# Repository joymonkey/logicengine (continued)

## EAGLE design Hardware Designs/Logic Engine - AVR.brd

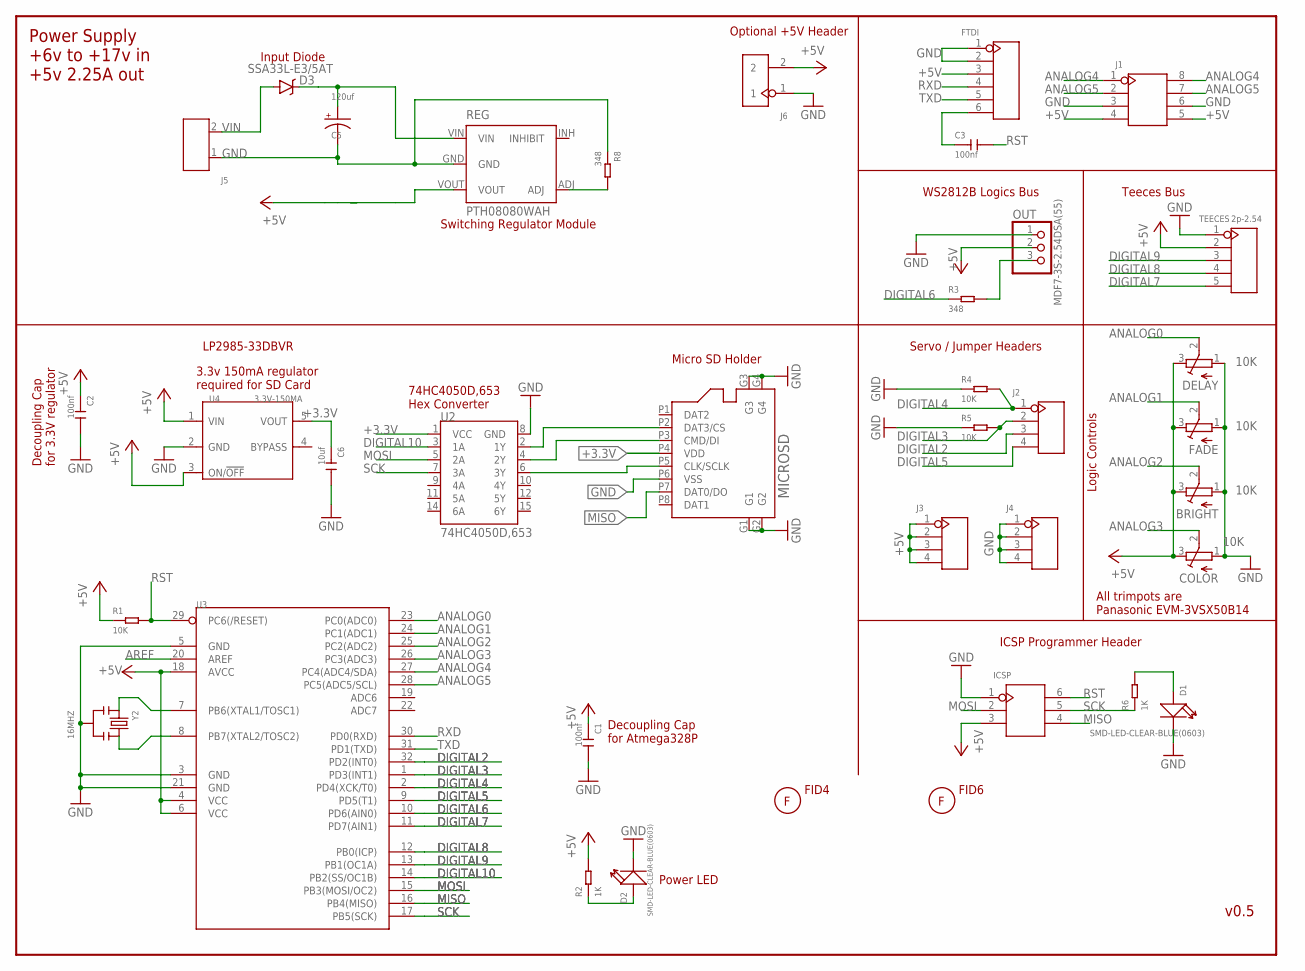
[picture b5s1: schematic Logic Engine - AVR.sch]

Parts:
BRIGHT: 10K; EVM3V
C1, C2, C3: 100nf; C0805
C5: 120uf; PANASONIC_D
C6: 10uf; C0805
COLOR: 10K; EVM3V
D1, D2: SMD-LED-CLEAR-BLUE(0603); LED-0603
D3: SSA33L-E3/5AT; SMA-DIODE
DELAY: 10K; EVM3V
FADE: 10K; EVM3V
FID4, FID6: FIDUCIAL; FIDUCIAL_G15
FTDI: DIP-BLACK-MALE-HEADER(6P-2.54); H6-2.54
ICSP: DIP-BLACK-MALE-HEADER(2X3P-2.54）-2.54; H2X3-2.54
J1: DIP-BLACK-MALE-HEADER-VERT(2X4P-2.54); H2X4-2.54
J2, J3, J4: DIP-BLACK-MALE-HEADER-VERT(4P-2.54); H4-2.54
J5: SCREW-TERMINAL-GREEN(2P-3.5); H2-3.5-7.0X7.0MM
J6: DIP-BLACK-MALE-HEADER-VERT(2P-2.54); H2-2.54
MICROSD: MICROSD47579-001; SD-47579-001
OUT: MDF7-3S-2.54DSA(55); MDF7_1X03
R1, R4, R5: 10K; R0603
R2, R6: 1K; R0603
R3, R8: 348; R0603
REG: PTH08080WAH; PTH08080W_TH
TEECES: 2p-2.54; H5-2.54
U2: 74HC4050D,653; SO016
U3: MCU-ATMEGA328P-AU(TQFP32); TQFP32-0.8-7X7MM
U4: 3.3V-150MA; SOT-23-5; MPN LP2985-33DBVR
Y2: 16MHZ; X3-SMD-3.6X1.3X0.8MM

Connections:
+3.3V: C6.1, MICROSD.P4 (VDD), U2.1 (VCC), U4.5 (VOUT)
+5V: BRIGHT.3 (E), C1.1, C2.1, COLOR.3 (E), DELAY.3 (E), FADE.3 (E), FTDI.3, ICSP.3, J1.4, J1.5, J3.1, J3.2, J3.3, J3.4, J6.2, OUT.2, R1.1, R2.2, REG.VOUT, TEECES.2, U3.4 (VCC), U3.6 (VCC), U3.18 (AVCC), U4.1 (VIN), U4.3 (ON/!OFF)
ANALOG0: DELAY.2 (S), U3.23 (PC0(ADC0))
ANALOG1: FADE.2 (S), U3.24 (PC1(ADC1))
ANALOG2: BRIGHT.2 (S), U3.25 (PC2(ADC2))
ANALOG3: COLOR.2 (S), U3.26 (PC3(ADC3))
ANALOG4: J1.1, J1.8, U3.27 (PC4(ADC4/SDA))
ANALOG5: J1.2, J1.7, U3.28 (PC5(ADC5/SCL))
AREF: U3.20 (AREF)
CS: MICROSD.P2 (DAT3/CS), U2.2 (1Y)
DATA_IN: MICROSD.P3 (CMD/DI), U2.4 (2Y)
DIGITAL2: J2.3, U3.32 (PD2(INT0))
DIGITAL3: J2.2, R5.2, U3.1 (PD3(INT1))
DIGITAL4: J2.1, R4.2, U3.2 (PD4(XCK/T0))
DIGITAL5: J2.4, U3.9 (PD5(T1))
DIGITAL6: R3.1, U3.10 (PD6(AIN0))
DIGITAL7: TEECES.5, U3.11 (PD7(AIN1))
DIGITAL8: TEECES.4, U3.12 (PB0(ICP))
DIGITAL9: TEECES.3, U3.13 (PB1(OC1A))
DIGITAL10: U2.3 (1A), U3.14 (PB2(SS/OC1B))
GND: BRIGHT.1 (A), C1.2, C2.2, C5.-, C6.2, COLOR.1 (A), D1.-, D2.-, DELAY.1 (A), FADE.1 (A), FTDI.1, FTDI.2, ICSP.1, J1.3, J1.6, J4.1, J4.2, J4.3, J4.4, J5.1, J6.1, MICROSD.G1, MICROSD.G2, MICROSD.G3, MICROSD.G4, MICROSD.P6 (VSS), OUT.1, R4.1, R5.1, R8.1, REG.GND, TEECES.1, U2.8 (GND), U3.3 (GND), U3.5 (GND), U3.21 (GND), U4.2 (GND), Y2.2
MISO: ICSP.4, MICROSD.P7 (DAT0/DO), U3.16 (PB4(MISO))
MOSI: ICSP.2, U2.5 (2A), U3.15 (PB3(MOSI/OC2))
unnamed: C5.+, D3.C, REG.VIN
unnamed: D1.+, R6.2
unnamed: D2.+, R2.1
unnamed: R8.2, REG.ADJ
unnamed: OUT.3, R3.2
unnamed: U3.7 (PB6(XTAL1/TOSC1)), Y2.1
unnamed: U3.8 (PB7(XTAL2/TOSC2)), Y2.3
RST: C3.2, ICSP.6, R1.2, U3.29 (PC6(/RESET))
RTS#: C3.1, FTDI.6
RXD: FTDI.4, U3.30 (PD0(RXD))
SCK: ICSP.5, R6.1, U2.7 (3A), U3.17 (PB5(SCK))
SCLK: MICROSD.P5 (CLK/SCLK), U2.6 (3Y)
TXD: FTDI.5, U3.31 (PD1(TXD))
VIN: D3.A, J5.2

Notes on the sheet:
v0.5
WS2812B Logics Bus
Power Supply +6v to +17v in +5v 2.25A out
Logic Controls
Teeces Bus
3.3v 150mA regulator required for SD Card
Servo / Jumper Headers
Optional +5V Header
74HC4050D,653 Hex Converter
LP2985-33DBVR
All trimpots are Panasonic EVM‑3VSX50B14
Micro SD Holder
Switching Regulator Module
Input Diode
Decoupling Cap for Atmega328P
Decoupling Cap for 3.3V regulator
ICSP Programmer Header
Power LED

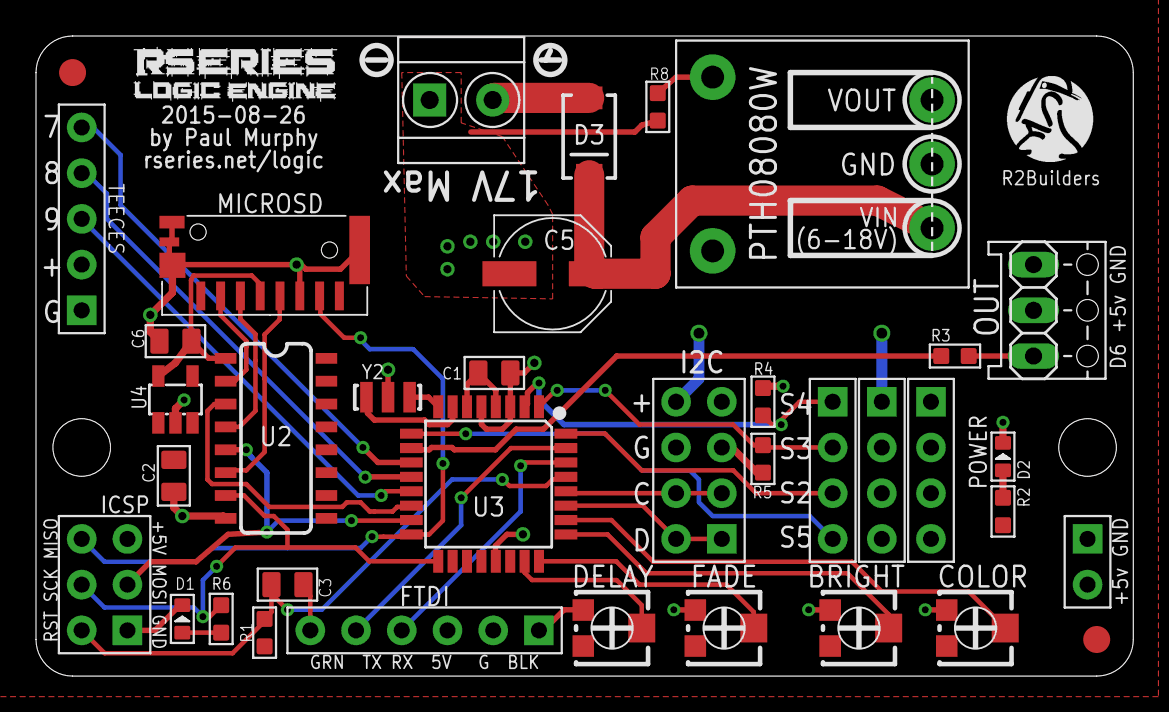
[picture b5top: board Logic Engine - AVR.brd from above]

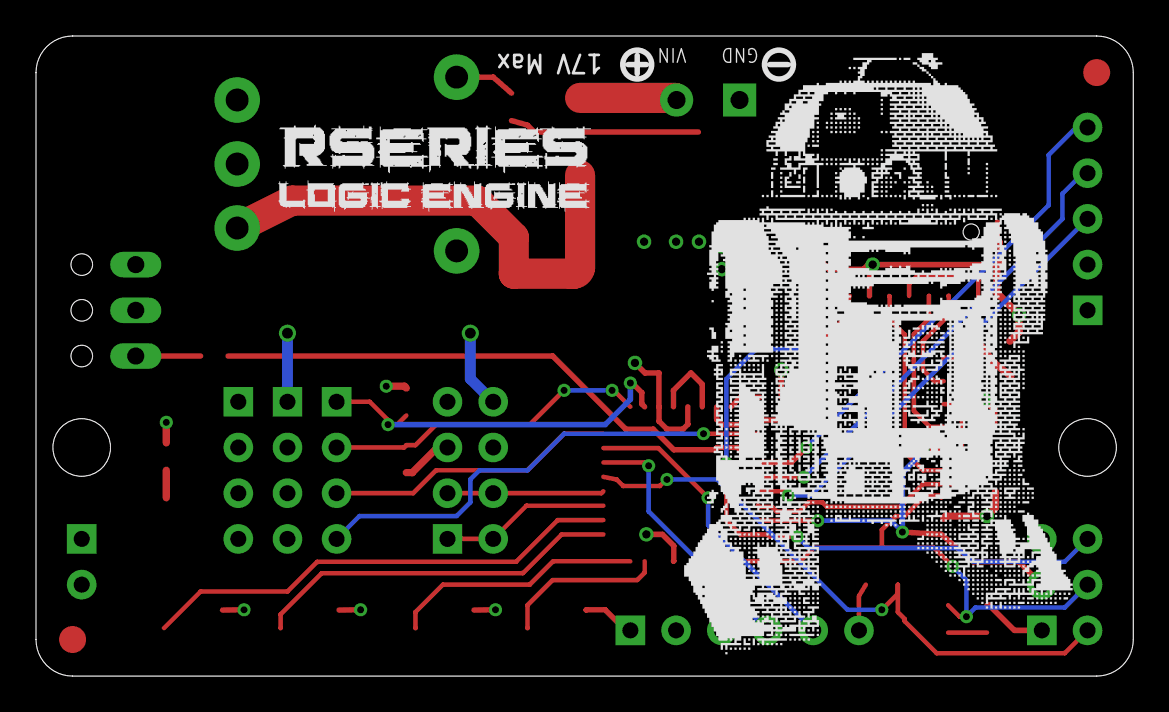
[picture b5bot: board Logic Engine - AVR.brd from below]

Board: 2 copper layers, 61.0 x 35.6 mm, 41 parts (2 on the bottom side), 36 nets.

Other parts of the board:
U$1: R2BUILDERS-LOGO
U$2: RSERIES-LE-LOGO2
U$3: RSERIES-LE-LOGO
U$4: R2-2LEG

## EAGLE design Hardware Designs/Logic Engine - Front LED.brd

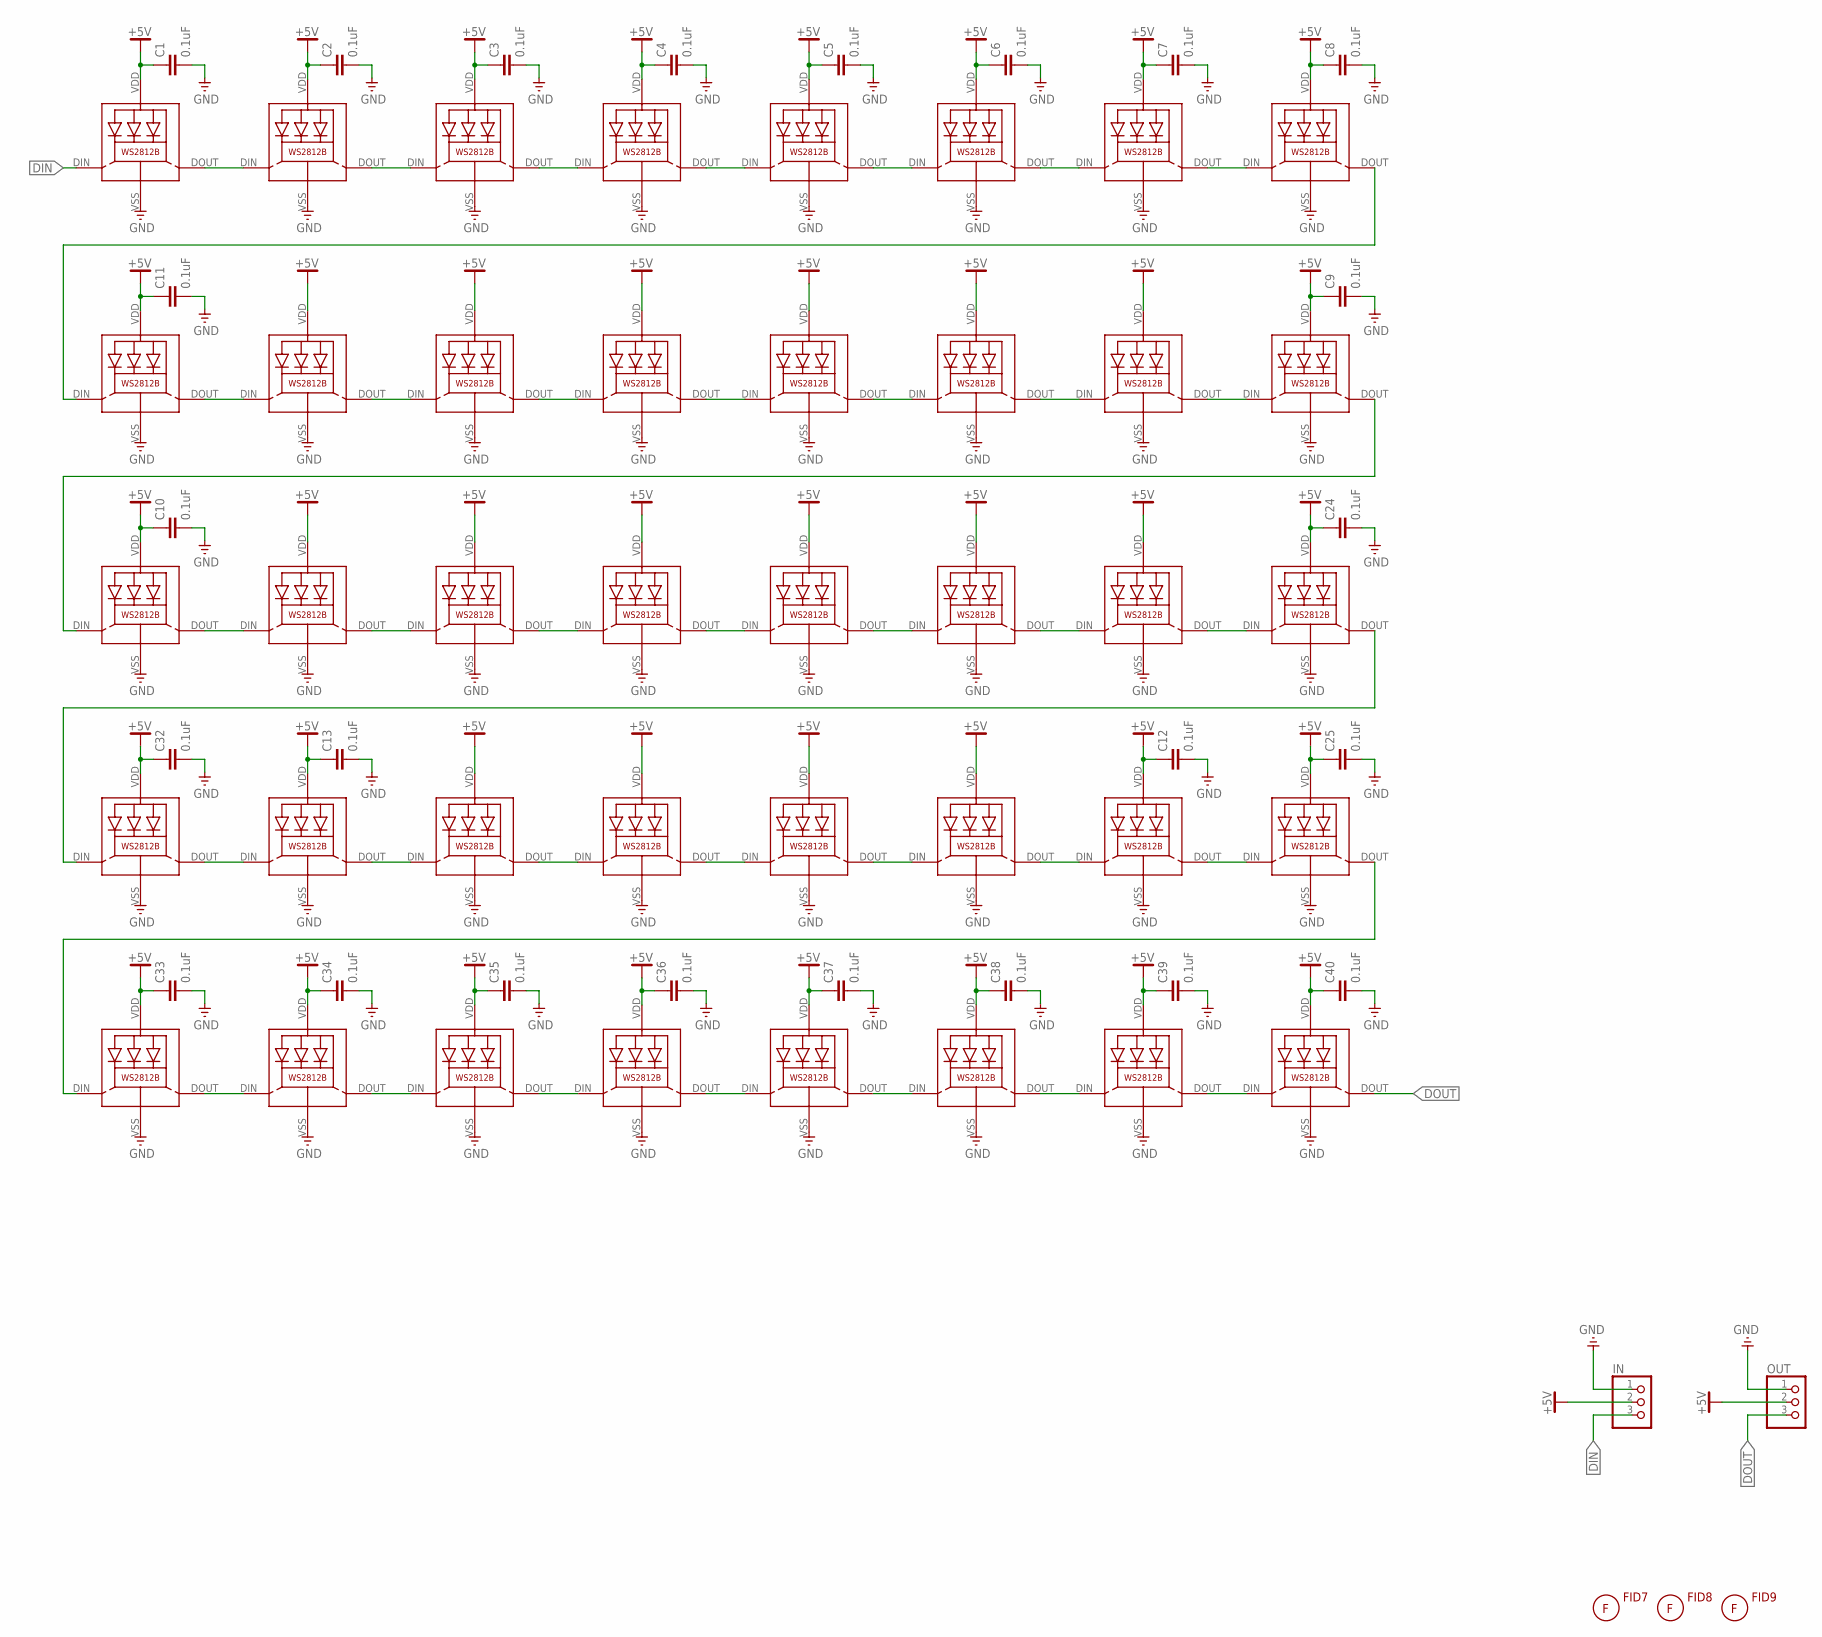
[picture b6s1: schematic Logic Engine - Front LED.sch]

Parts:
C1, C2, C3, C4, C5, C6, C7, C8, C9, C10, C11, C12, C13, C24, C25, C32, C33, C34, C35, C36, C37, C38, C39, C40: 0.1uF; 0603-CAP
FID7, FID8, FID9: FIDUCIAL; FIDUCIAL_G15
IN: PINHD-1X3; 1X03
L1, L2, L3, L4, L5, L6, L7, L8, L9, L10, L11, L12, L13, L14, L15, L16, L17, L18, L19, L20, L21, L22, L23, L24, L25, L26, L27, L28, L29, L30, L31, L32, L33, L34, L35, L36, L37, L38, L39, L40: WS2812B
OUT: PINHD-1X3; 1X03

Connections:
+5V: C1.1, C2.1, C3.1, C4.1, C5.1, C6.1, C7.1, C8.1, C9.1, C10.1, C11.1, C12.1, C13.1, C24.1, C25.1, C32.1, C33.1, C34.1, C35.1, C36.1, C37.1, C38.1, C39.1, C40.1, IN.2, L1.VDD, L2.VDD, L3.VDD, L4.VDD, L5.VDD, L6.VDD, L7.VDD, L8.VDD, L9.VDD, L10.VDD, L11.VDD, L12.VDD, L13.VDD, L14.VDD, L15.VDD, L16.VDD, L17.VDD, L18.VDD, L19.VDD, L20.VDD, L21.VDD, L22.VDD, L23.VDD, L24.VDD, L25.VDD, L26.VDD, L27.VDD, L28.VDD, L29.VDD, L30.VDD, L31.VDD, L32.VDD, L33.VDD, L34.VDD, L35.VDD, L36.VDD, L37.VDD, L38.VDD, L39.VDD, L40.VDD, OUT.2
DIN: IN.3, L1.DIN (DI)
DOUT: L40.DOUT (DO), OUT.3
GND: C1.2, C2.2, C3.2, C4.2, C5.2, C6.2, C7.2, C8.2, C9.2, C10.2, C11.2, C12.2, C13.2, C24.2, C25.2, C32.2, C33.2, C34.2, C35.2, C36.2, C37.2, C38.2, C39.2, C40.2, IN.1, L1.VSS (GND), L2.VSS (GND), L3.VSS (GND), L4.VSS (GND), L5.VSS (GND), L6.VSS (GND), L7.VSS (GND), L8.VSS (GND), L9.VSS (GND), L10.VSS (GND), L11.VSS (GND), L12.VSS (GND), L13.VSS (GND), L14.VSS (GND), L15.VSS (GND), L16.VSS (GND), L17.VSS (GND), L18.VSS (GND), L19.VSS (GND), L20.VSS (GND), L21.VSS (GND), L22.VSS (GND), L23.VSS (GND), L24.VSS (GND), L25.VSS (GND), L26.VSS (GND), L27.VSS (GND), L28.VSS (GND), L29.VSS (GND), L30.VSS (GND), L31.VSS (GND), L32.VSS (GND), L33.VSS (GND), L34.VSS (GND), L35.VSS (GND), L36.VSS (GND), L37.VSS (GND), L38.VSS (GND), L39.VSS (GND), L40.VSS (GND), OUT.1
unnamed: L9.DOUT (DO), L10.DIN (DI)
unnamed: L10.DOUT (DO), L11.DIN (DI)
unnamed: L11.DOUT (DO), L12.DIN (DI)
unnamed: L12.DOUT (DO), L13.DIN (DI)
unnamed: L13.DOUT (DO), L14.DIN (DI)
unnamed: L14.DOUT (DO), L15.DIN (DI)
unnamed: L15.DOUT (DO), L16.DIN (DI)
unnamed: L17.DOUT (DO), L18.DIN (DI)
unnamed: L18.DOUT (DO), L19.DIN (DI)
unnamed: L19.DOUT (DO), L20.DIN (DI)
unnamed: L20.DOUT (DO), L21.DIN (DI)
unnamed: L21.DOUT (DO), L22.DIN (DI)
unnamed: L22.DOUT (DO), L23.DIN (DI)
unnamed: L23.DOUT (DO), L24.DIN (DI)
unnamed: L25.DOUT (DO), L26.DIN (DI)
unnamed: L26.DOUT (DO), L27.DIN (DI)
unnamed: L27.DOUT (DO), L28.DIN (DI)
unnamed: L28.DOUT (DO), L29.DIN (DI)
unnamed: L29.DOUT (DO), L30.DIN (DI)
unnamed: L30.DOUT (DO), L31.DIN (DI)
unnamed: L31.DOUT (DO), L32.DIN (DI)
unnamed: L33.DOUT (DO), L34.DIN (DI)
unnamed: L34.DOUT (DO), L35.DIN (DI)
unnamed: L35.DOUT (DO), L36.DIN (DI)
unnamed: L36.DOUT (DO), L37.DIN (DI)
unnamed: L37.DOUT (DO), L38.DIN (DI)
unnamed: L38.DOUT (DO), L39.DIN (DI)
unnamed: L39.DOUT (DO), L40.DIN (DI)
unnamed: L8.DOUT (DO), L9.DIN (DI)
unnamed: L16.DOUT (DO), L17.DIN (DI)
unnamed: L24.DOUT (DO), L25.DIN (DI)
unnamed: L32.DOUT (DO), L33.DIN (DI)
unnamed: L1.DOUT (DO), L2.DIN (DI)
unnamed: L2.DOUT (DO), L3.DIN (DI)
unnamed: L3.DOUT (DO), L4.DIN (DI)
unnamed: L4.DOUT (DO), L5.DIN (DI)
unnamed: L5.DOUT (DO), L6.DIN (DI)
unnamed: L6.DOUT (DO), L7.DIN (DI)
unnamed: L7.DOUT (DO), L8.DIN (DI)

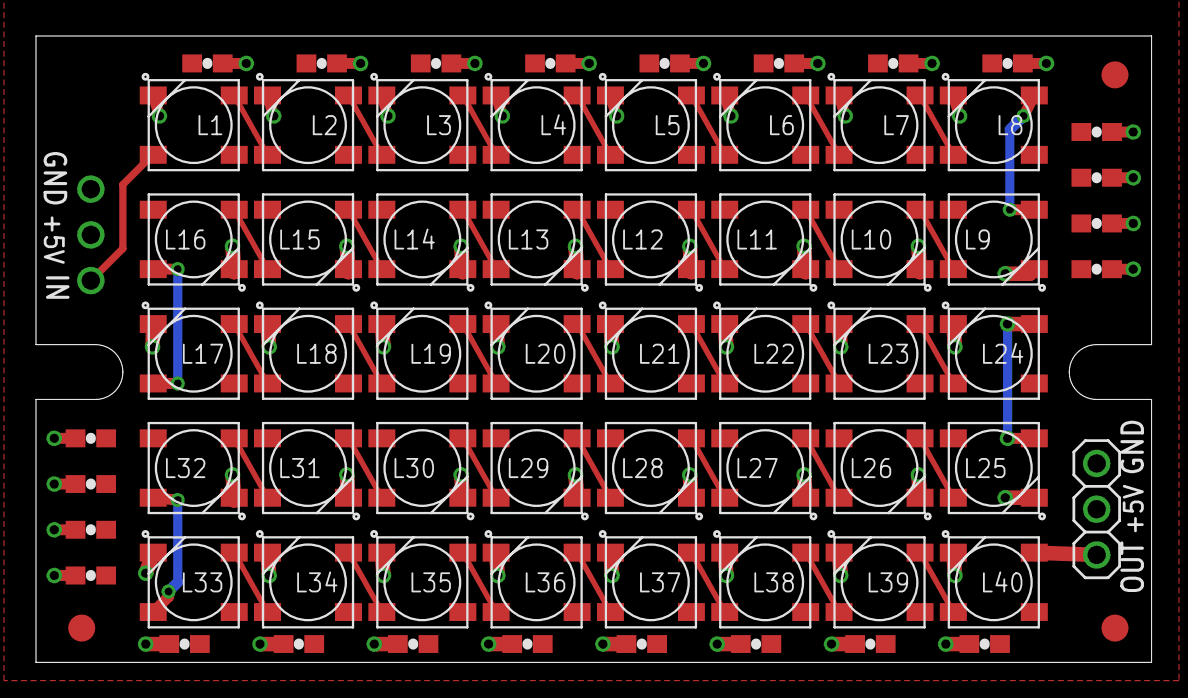
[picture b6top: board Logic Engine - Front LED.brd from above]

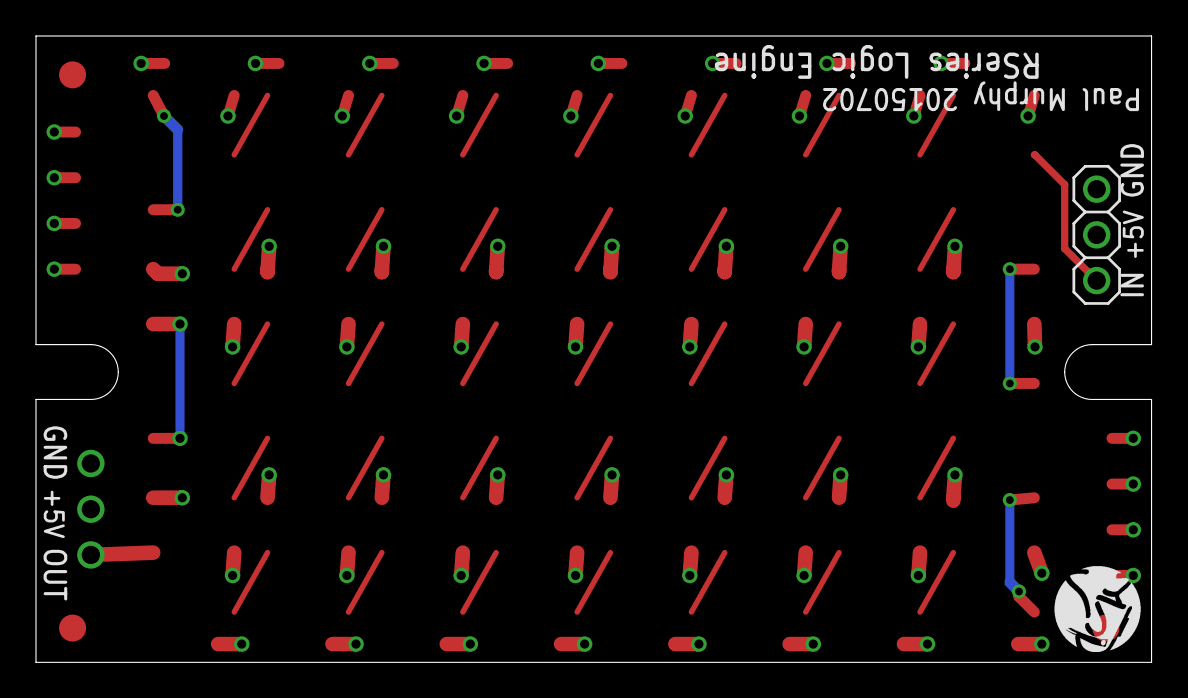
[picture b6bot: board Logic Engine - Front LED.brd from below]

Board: 2 copper layers, 62.0 x 34.8 mm, 70 parts (2 on the bottom side), 43 nets.

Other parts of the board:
U$2: R2BUILDERS-LOGO

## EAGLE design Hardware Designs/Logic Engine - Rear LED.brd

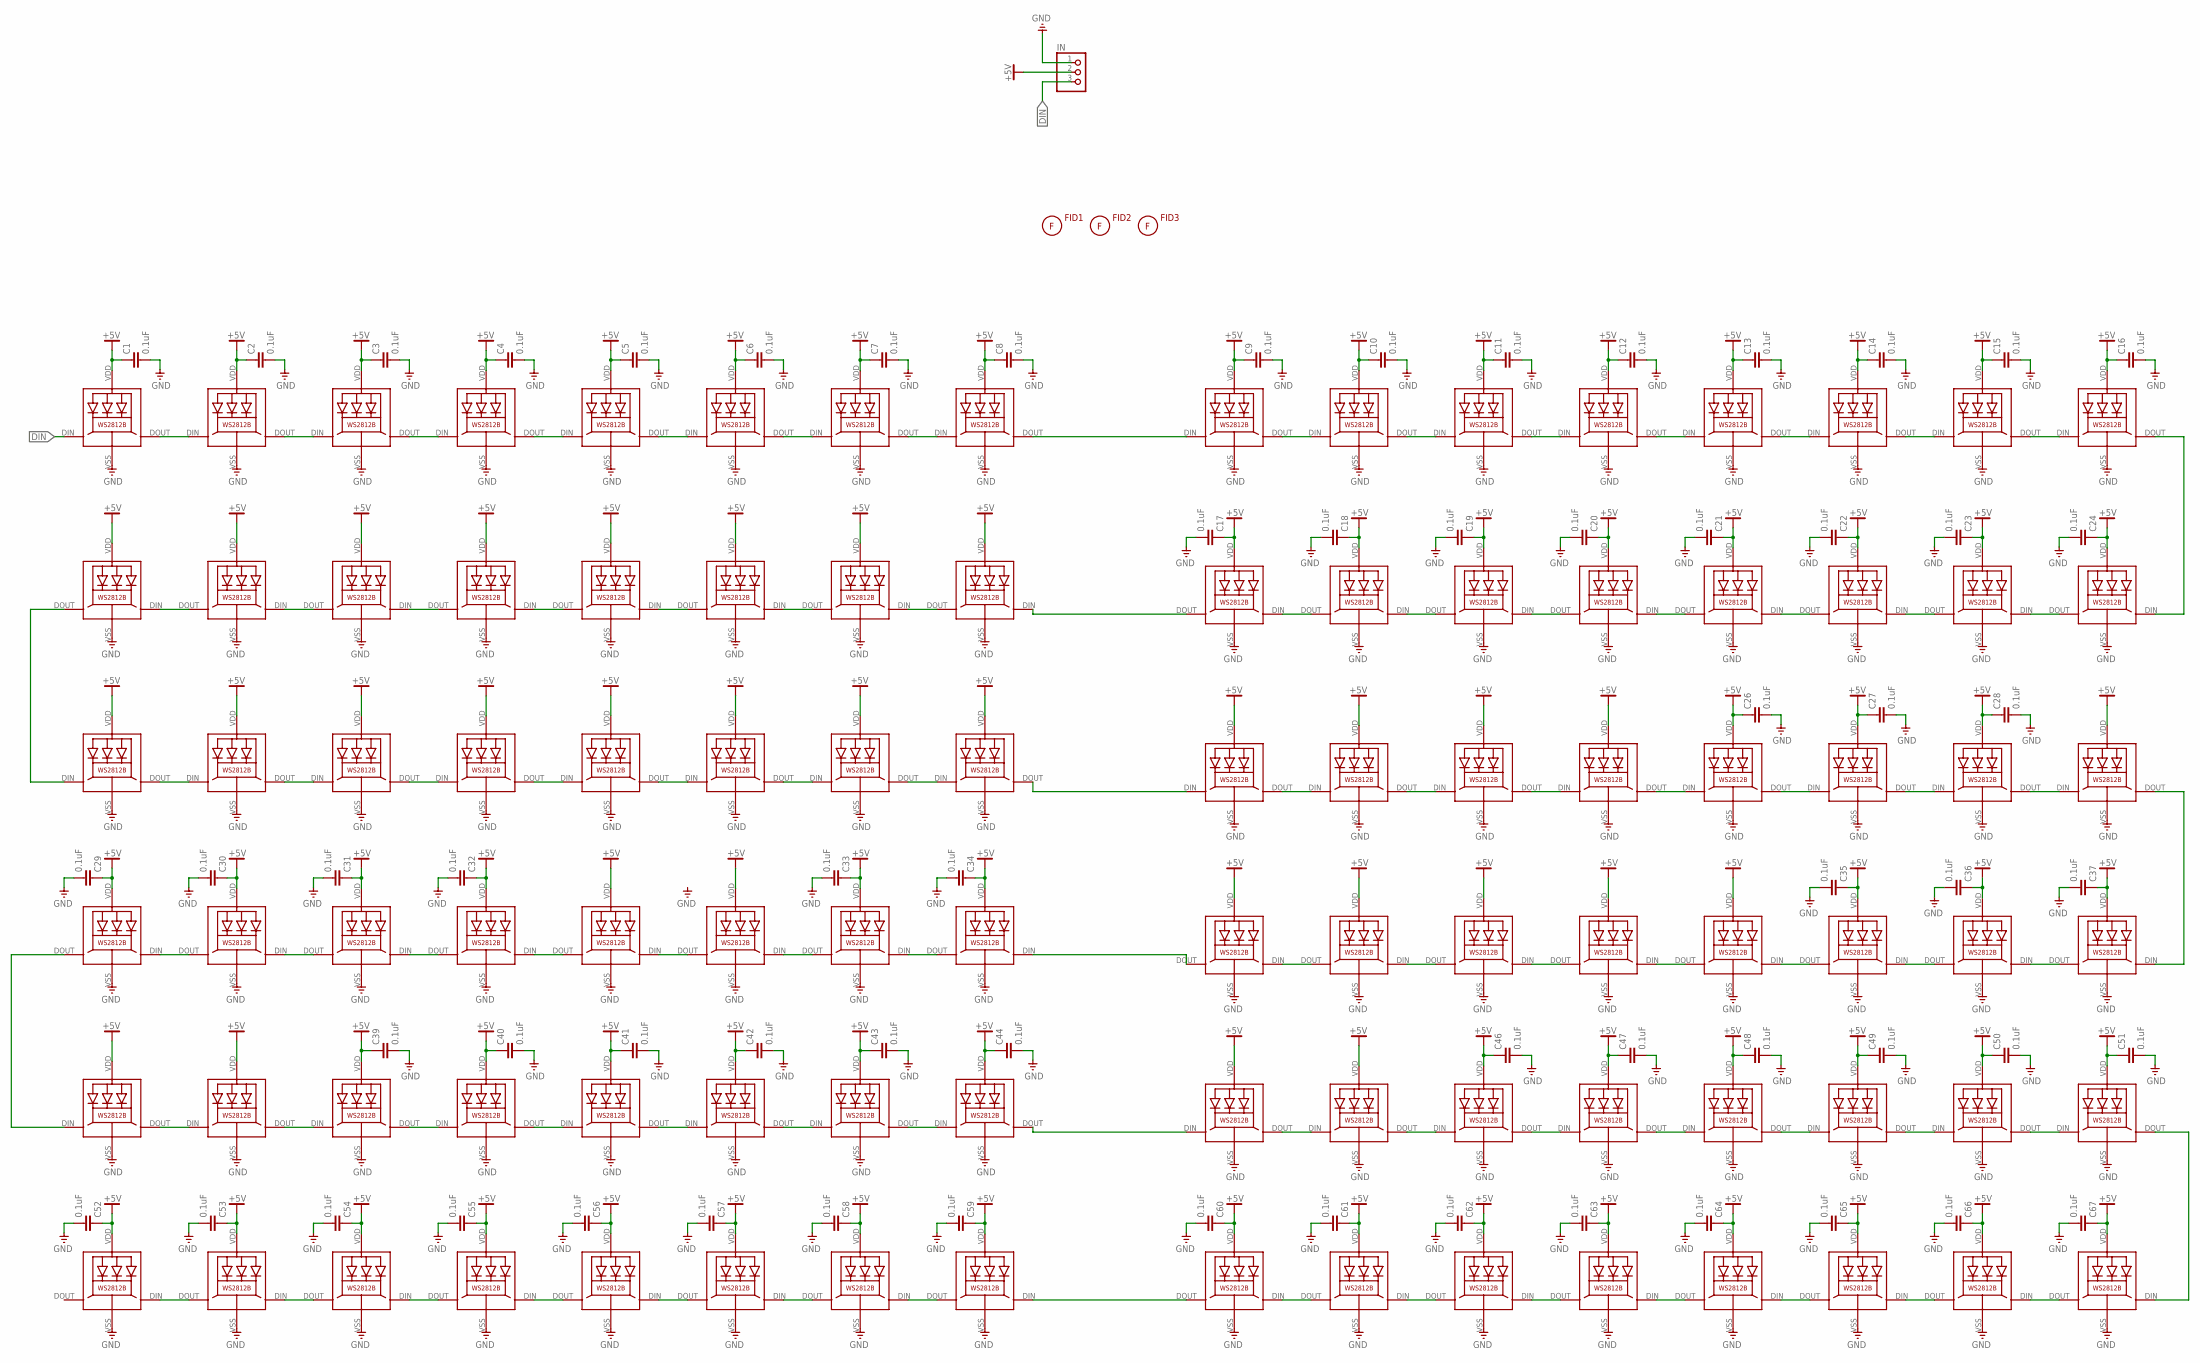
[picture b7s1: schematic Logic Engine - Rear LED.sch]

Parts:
C1, C2, C3, C4, C5, C6, C7, C8, C9, C10, C11, C12, C13, C14, C15, C16, C17, C18, C19, C20, C21, C22, C23, C24, C26, C27, C28, C29, C30, C31, C32, C33, C34, C35, C36, C37, C39, C40, C41, C42, C43, C44, C46, C47, C48, C49, C50, C51, C52, C53, C54, C55, C56, C57, C58, C59, C60, C61, C62, C63, C64, C65, C66, C67: 0.1uF; 0603-CAP
FID1, FID2, FID3: FIDUCIAL; FIDUCIAL_G15
IN: PINHD-1X3; 1X03
L1, L2, L3, L4, L5, L6, L7, L8, L9, L10, L11, L12, L13, L14, L15, L16, L17, L18, L19, L20, L21, L22, L23, L24, L25, L26, L27, L28, L29, L30, L31, L32, L33, L34, L35, L36, L37, L38, L39, L40, L41, L42, L43, L44, L45, L46, L47, L48, L49, L50, L51, L52, L53, L54, L55, L56, L57, L58, L59, L60, L61, L62, L63, L64, L65, L66, L67, L68, L69, L70, L71, L72, L73, L74, L75, L76, L77, L78, L79, L80, L81, L82, L83, L84, L85, L86, L87, L88, L89, L90, L91, L92, L93, L94, L95, L96: WS2812B

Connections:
+5V: C1.1, C2.1, C3.1, C4.1, C5.1, C6.1, C7.1, C8.1, C9.1, C10.1, C11.1, C12.1, C13.1, C14.1, C15.1, C16.1, C17.1, C18.1, C19.1, C20.1, C21.1, C22.1, C23.1, C24.1, C26.1, C27.1, C28.1, C29.1, C30.1, C31.1, C32.1, C33.1, C34.1, C35.1, C36.1, C37.1, C39.1, C40.1, C41.1, C42.1, C43.1, C44.1, C46.1, C47.1, C48.1, C49.1, C50.1, C51.1, C52.1, C53.1, C54.1, C55.1, C56.1, C57.1, C58.1, C59.1, C60.1, C61.1, C62.1, C63.1, C64.1, C65.1, C66.1, C67.1, IN.2, L1.VDD, L2.VDD, L3.VDD, L4.VDD, L5.VDD, L6.VDD, L7.VDD, L8.VDD, L9.VDD, L10.VDD, L11.VDD, L12.VDD, L13.VDD, L14.VDD, L15.VDD, L16.VDD, L17.VDD, L18.VDD, L19.VDD, L20.VDD, L21.VDD, L22.VDD, L23.VDD, L24.VDD, L25.VDD, L26.VDD, L27.VDD, L28.VDD, L29.VDD, L30.VDD, L31.VDD, L32.VDD, L33.VDD, L34.VDD, L35.VDD, L36.VDD, L37.VDD, L38.VDD, L39.VDD, L40.VDD, L41.VDD, L42.VDD, L43.VDD, L44.VDD, L45.VDD, L46.VDD, L47.VDD, L48.VDD, L49.VDD, L50.VDD, L51.VDD, L52.VDD, L53.VDD, L54.VDD, L55.VDD, L56.VDD, L57.VDD, L58.VDD, L59.VDD, L60.VDD, L61.VDD, L62.VDD, L63.VDD, L64.VDD, L65.VDD, L66.VDD, L67.VDD, L68.VDD, L69.VDD, L70.VDD, L71.VDD, L72.VDD, L73.VDD, L74.VDD, L75.VDD, L76.VDD, L77.VDD, L78.VDD, L79.VDD, L80.VDD, L81.VDD, L82.VDD, L83.VDD, L84.VDD, L85.VDD, L86.VDD, L87.VDD, L88.VDD, L89.VDD, L90.VDD, L91.VDD, L92.VDD, L93.VDD, L94.VDD, L95.VDD, L96.VDD
DIN: IN.3, L1.DIN (DI)
GND: C1.2, C2.2, C3.2, C4.2, C5.2, C6.2, C7.2, C8.2, C9.2, C10.2, C11.2, C12.2, C13.2, C14.2, C15.2, C16.2, C17.2, C18.2, C19.2, C20.2, C21.2, C22.2, C23.2, C24.2, C26.2, C27.2, C28.2, C29.2, C30.2, C31.2, C32.2, C33.2, C34.2, C35.2, C36.2, C37.2, C39.2, C40.2, C41.2, C42.2, C43.2, C44.2, C46.2, C47.2, C48.2, C49.2, C50.2, C51.2, C52.2, C53.2, C54.2, C55.2, C56.2, C57.2, C58.2, C59.2, C60.2, C61.2, C62.2, C63.2, C64.2, C65.2, C66.2, C67.2, IN.1, L1.VSS (GND), L2.VSS (GND), L3.VSS (GND), L4.VSS (GND), L5.VSS (GND), L6.VSS (GND), L7.VSS (GND), L8.VSS (GND), L9.VSS (GND), L10.VSS (GND), L11.VSS (GND), L12.VSS (GND), L13.VSS (GND), L14.VSS (GND), L15.VSS (GND), L16.VSS (GND), L17.VSS (GND), L18.VSS (GND), L19.VSS (GND), L20.VSS (GND), L21.VSS (GND), L22.VSS (GND), L23.VSS (GND), L24.VSS (GND), L25.VSS (GND), L26.VSS (GND), L27.VSS (GND), L28.VSS (GND), L29.VSS (GND), L30.VSS (GND), L31.VSS (GND), L32.VSS (GND), L33.VSS (GND), L34.VSS (GND), L35.VSS (GND), L36.VSS (GND), L37.VSS (GND), L38.VSS (GND), L39.VSS (GND), L40.VSS (GND), L41.VSS (GND), L42.VSS (GND), L43.VSS (GND), L44.VSS (GND), L45.VSS (GND), L46.VSS (GND), L47.VSS (GND), L48.VSS (GND), L49.VSS (GND), L50.VSS (GND), L51.VSS (GND), L52.VSS (GND), L53.VSS (GND), L54.VSS (GND), L55.VSS (GND), L56.VSS (GND), L57.VSS (GND), L58.VSS (GND), L59.VSS (GND), L60.VSS (GND), L61.VSS (GND), L62.VSS (GND), L63.VSS (GND), L64.VSS (GND), L65.VSS (GND), L66.VSS (GND), L67.VSS (GND), L68.VSS (GND), L69.VSS (GND), L70.VSS (GND), L71.VSS (GND), L72.VSS (GND), L73.VSS (GND), L74.VSS (GND), L75.VSS (GND), L76.VSS (GND), L77.VSS (GND), L78.VSS (GND), L79.VSS (GND), L80.VSS (GND), L81.VSS (GND), L82.VSS (GND), L83.VSS (GND), L84.VSS (GND), L85.VSS (GND), L86.VSS (GND), L87.VSS (GND), L88.VSS (GND), L89.VSS (GND), L90.VSS (GND), L91.VSS (GND), L92.VSS (GND), L93.VSS (GND), L94.VSS (GND), L95.VSS (GND), L96.VSS (GND)
unnamed: L23.DIN (DI), L24.DOUT (DO)
unnamed: L22.DIN (DI), L23.DOUT (DO)
unnamed: L21.DIN (DI), L22.DOUT (DO)
unnamed: L20.DIN (DI), L21.DOUT (DO)
unnamed: L19.DIN (DI), L20.DOUT (DO)
unnamed: L18.DIN (DI), L19.DOUT (DO)
unnamed: L17.DIN (DI), L18.DOUT (DO)
unnamed: L33.DOUT (DO), L34.DIN (DI)
unnamed: L34.DOUT (DO), L35.DIN (DI)
unnamed: L35.DOUT (DO), L36.DIN (DI)
unnamed: L36.DOUT (DO), L37.DIN (DI)
unnamed: L37.DOUT (DO), L38.DIN (DI)
unnamed: L38.DOUT (DO), L39.DIN (DI)
unnamed: L39.DOUT (DO), L40.DIN (DI)
unnamed: L55.DIN (DI), L56.DOUT (DO)
unnamed: L54.DIN (DI), L55.DOUT (DO)
unnamed: L53.DIN (DI), L54.DOUT (DO)
unnamed: L52.DIN (DI), L53.DOUT (DO)
unnamed: L51.DIN (DI), L52.DOUT (DO)
unnamed: L50.DIN (DI), L51.DOUT (DO)
unnamed: L49.DIN (DI), L50.DOUT (DO)
unnamed: L65.DOUT (DO), L66.DIN (DI)
unnamed: L66.DOUT (DO), L67.DIN (DI)
unnamed: L67.DOUT (DO), L68.DIN (DI)
unnamed: L68.DOUT (DO), L69.DIN (DI)
unnamed: L69.DOUT (DO), L70.DIN (DI)
unnamed: L70.DOUT (DO), L71.DIN (DI)
unnamed: L71.DOUT (DO), L72.DIN (DI)
unnamed: L24.DIN (DI), L25.DOUT (DO)
unnamed: L17.DOUT (DO), L33.DIN (DI)
unnamed: L40.DOUT (DO), L41.DIN (DI)
unnamed: L48.DOUT (DO), L64.DIN (DI)
unnamed: L87.DIN (DI), L88.DOUT (DO)
unnamed: L86.DIN (DI), L87.DOUT (DO)
unnamed: L85.DIN (DI), L86.DOUT (DO)
unnamed: L84.DIN (DI), L85.DOUT (DO)
unnamed: L83.DIN (DI), L84.DOUT (DO)
unnamed: L82.DIN (DI), L83.DOUT (DO)
unnamed: L81.DIN (DI), L82.DOUT (DO)
unnamed: L1.DOUT (DO), L2.DIN (DI)
unnamed: L2.DOUT (DO), L3.DIN (DI)
unnamed: L3.DOUT (DO), L4.DIN (DI)
unnamed: L4.DOUT (DO), L5.DIN (DI)
unnamed: L5.DOUT (DO), L6.DIN (DI)
unnamed: L6.DOUT (DO), L7.DIN (DI)
unnamed: L7.DOUT (DO), L8.DIN (DI)
unnamed: L56.DIN (DI), L57.DOUT (DO)
unnamed: L9.DOUT (DO), L10.DIN (DI)
unnamed: L10.DOUT (DO), L11.DIN (DI)
unnamed: L11.DOUT (DO), L12.DIN (DI)
unnamed: L12.DOUT (DO), L13.DIN (DI)
unnamed: L13.DOUT (DO), L14.DIN (DI)
unnamed: L14.DOUT (DO), L15.DIN (DI)
unnamed: L15.DOUT (DO), L16.DIN (DI)
unnamed: L31.DIN (DI), L32.DOUT (DO)
unnamed: L30.DIN (DI), L31.DOUT (DO)
unnamed: L29.DIN (DI), L30.DOUT (DO)
unnamed: L28.DIN (DI), L29.DOUT (DO)
unnamed: L27.DIN (DI), L28.DOUT (DO)
unnamed: L26.DIN (DI), L27.DOUT (DO)
unnamed: L25.DIN (DI), L26.DOUT (DO)
unnamed: L41.DOUT (DO), L42.DIN (DI)
unnamed: L42.DOUT (DO), L43.DIN (DI)
unnamed: L43.DOUT (DO), L44.DIN (DI)
unnamed: L44.DOUT (DO), L45.DIN (DI)
unnamed: L45.DOUT (DO), L46.DIN (DI)
unnamed: L46.DOUT (DO), L47.DIN (DI)
unnamed: L47.DOUT (DO), L48.DIN (DI)
unnamed: L63.DIN (DI), L64.DOUT (DO)
unnamed: L62.DIN (DI), L63.DOUT (DO)
unnamed: L61.DIN (DI), L62.DOUT (DO)
unnamed: L60.DIN (DI), L61.DOUT (DO)
unnamed: L59.DIN (DI), L60.DOUT (DO)
unnamed: L58.DIN (DI), L59.DOUT (DO)
unnamed: L57.DIN (DI), L58.DOUT (DO)
unnamed: L73.DOUT (DO), L74.DIN (DI)
unnamed: L74.DOUT (DO), L75.DIN (DI)
unnamed: L75.DOUT (DO), L76.DIN (DI)
unnamed: L76.DOUT (DO), L77.DIN (DI)
unnamed: L77.DOUT (DO), L78.DIN (DI)
unnamed: L78.DOUT (DO), L79.DIN (DI)
unnamed: L79.DOUT (DO), L80.DIN (DI)
unnamed: L95.DIN (DI), L96.DOUT (DO)
unnamed: L94.DIN (DI), L95.DOUT (DO)
unnamed: L93.DIN (DI), L94.DOUT (DO)
unnamed: L92.DIN (DI), L93.DOUT (DO)
unnamed: L91.DIN (DI), L92.DOUT (DO)
unnamed: L90.DIN (DI), L91.DOUT (DO)
unnamed: L89.DIN (DI), L90.DOUT (DO)
unnamed: L8.DOUT (DO), L9.DIN (DI)
unnamed: L16.DOUT (DO), L32.DIN (DI)
unnamed: L49.DOUT (DO), L65.DIN (DI)
unnamed: L72.DOUT (DO), L73.DIN (DI)
unnamed: L80.DOUT (DO), L96.DIN (DI)
unnamed: L88.DIN (DI), L89.DOUT (DO)

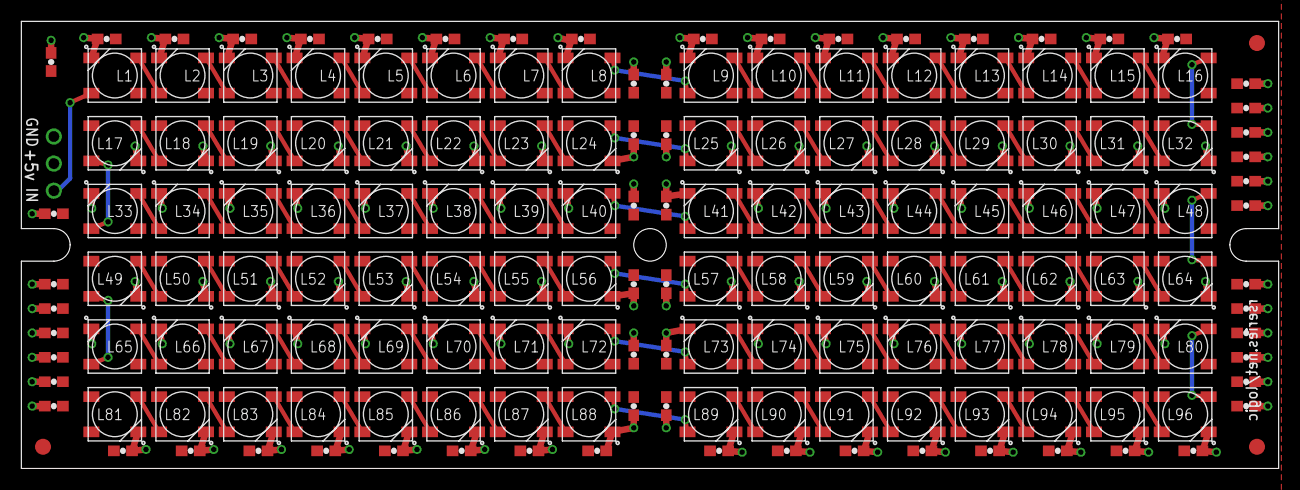
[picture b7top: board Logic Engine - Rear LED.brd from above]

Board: 2 copper layers, 117.9 x 41.9 mm, 164 parts (1 on the bottom side), 98 nets.

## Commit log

2015-06-11 :confetti_ball: Added .gitattributes & .gitignore files
2015-06-11 initial upload of older Logic Engine stuff
2015-06-11 added rear LED board (Eagle format)
2015-06-11 updated Front LED board to current version
2015-06-11 added Eagle backup files to ignore list
2015-06-24 Updated AVR board to production version
2015-07-27 added bare bones logic sketch
2015-08-03 Uploaded old "v9" sketch
2015-10-19 Revised Front LED board slightly
    Front LED board had it's mounting holes & pin headers moved down 0.04
    inches. When mounting in dome this should give a little extra clearance
    (0.08 inches) between the front boards.
2015-10-19 Updated AVR board slightly
    Small revision to AVR board for late 2015 run (first change since these
    boards were first run). Added resistor on LED output, removed reset
    switch, removed 'power' jumper, moved stuff around, routed a little
    smarter (I think), added fancy silkscreen art. Functionality-wise this
    is identical to the previous version.
2016-01-11 moving wiki images to Github
2016-10-07 More missing img fixes
2016-10-07 another img
2016-12-14 Added new hardware designs (Reactor & LED boards)
2016-12-15 updated FastLED library to 3.1.3
2016-12-20 added Teensy Reactor diagram
2017-01-24 Added PDF assembly guide
2017-06-03 Added basic Teensy Reactor sketch
2017-06-03 Fixed readme formatting
2017-06-25 small Teensy Reactor sketch update
2017-08-23 updated PDF instruction sheet
2017-12-02 added slim AVR sketch
2018-02-10 added throwback Teeces PSI design files
2018-03-31 added option support for PSI, holos, magicpanel, and servos
    This is optional support for Teeces PSIs, Magicpanel, Holo LEDs, and panel servos. Still need to decide on which serial commands to use for servos and need to add holo servo control.
2018-04-08 Added v0.7 sketch with Teeces PSI support
2018-04-08 fixed I2C silkscreen error
2018-09-15 Added ReactorZero sketch
2018-10-24 Added newer assembly instruction sheet
2018-12-20 fixed microphone function typo (thanks Mimir!)
2019-01-31 fixed baud rate
2019-10-20 added Reactor Zero (oops)
2019-12-30 Added Mounty Thing STL and PDF files
2020-03-06 updated Teeces PSI board design
    Moved signal routing away from board edge
2020-05-10 added some images to docs
2020-09-15 Added Reactor Zero V6 image
2021-01-03 added V6 cheat sheet
2021-01-03 Added basic V6 sketch
2021-09-29 added WREACTOR32 image
2021-09-29 added new image of WREACTOR32 board
2021-09-29 fixed image typo
2021-10-14 added wreactor32 firmware files and images
2021-10-14 added image thumbnails
2021-10-17 updated FW, with ability to turn off wifi using button
2022-04-09 Added firmware with less bright default values
    Unless otherwise tweaked by the user, these defaults should cause the whole system to consume less than 500mA at 5V, which should cause fewer problems for people testing via a Micro USB cable.
2022-04-10 added tweaked WReactor32 firmware
    fixed error in firware preventing rear logic adjustment from the board inputs, adjusted default brightness settings to fix current-draw issue when testing via a micro USB cable.
2022-04-26 Create LEngine_20220426.bin
    slight tweak to WReactor32 firmware, to make connections simpler for user of old 96-LED rear logics.
2024-01-27 added photos of Serial1 rework
2025-03-02 added WReactor32 firmware bin for RGBW and AstroPixelsPSI
